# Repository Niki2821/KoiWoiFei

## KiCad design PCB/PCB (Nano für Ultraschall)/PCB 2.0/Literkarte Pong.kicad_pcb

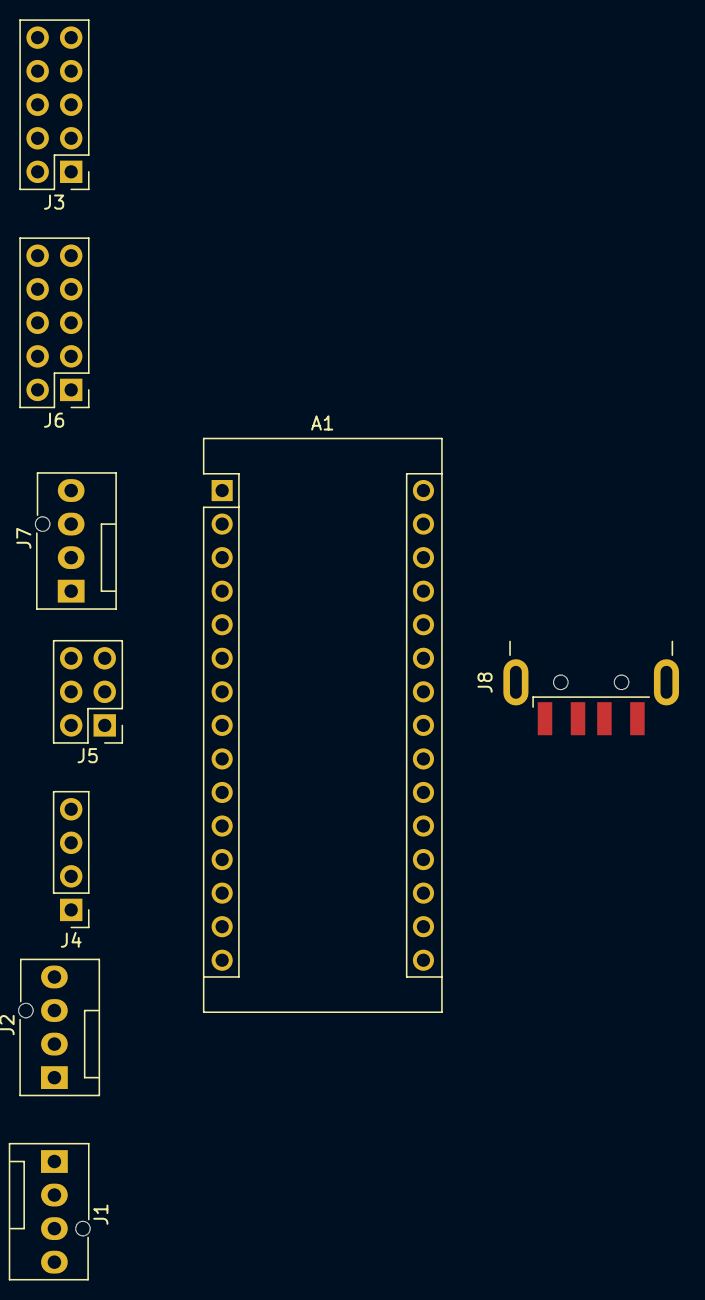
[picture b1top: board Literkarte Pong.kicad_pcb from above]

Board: 2 copper layers, 9 parts (0 on the bottom side), 16 nets, no tracks yet.

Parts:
A1: Arduino_Nano_v3.x; Arduino_Nano
J1: U4; FanPinHeader_1x04_P2.54mm_Vertical
J2: U3; FanPinHeader_1x04_P2.54mm_Vertical
J3, J6: Conn_02x05_Odd_Even; PinHeader_2x05_P2.54mm_Vertical
J4: U2; PinHeader_1x04_P2.54mm_Vertical
J5: Conn_02x03_Odd_Even; PinHeader_2x03_P2.54mm_Vertical
J7: U1; FanPinHeader_1x04_P2.54mm_Vertical
J8: USB_B; USB_A_CNCTech_1001-011-01101_Horizontal

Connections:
GND: A1.29, J1.1, J2.4, J3.1, J3.2, J4.4, J5.5, J5.6, J6.1, J6.2, J7.4, J8.4
unnamed: A1.1, J3.7, J3.8
unnamed: A1.2, J6.7, J6.8
unnamed: A1.5, J7.3
unnamed: A1.6, J7.2
unnamed: A1.7, J5.3, J5.4
unnamed: A1.8, J4.3
unnamed: A1.9, J4.2
unnamed: A1.10, J2.3
unnamed: A1.11, J2.2
unnamed: A1.12, J1.2
unnamed: A1.13, J1.3
unnamed: J3.3, J3.4
unnamed: J3.5, J3.6, J6.5, J6.6
unnamed: J6.3, J6.4
VCC: A1.27, J1.4, J2.1, J3.9, J3.10, J4.1, J5.1, J5.2, J6.9, J6.10, J7.1, J8.1

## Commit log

2022-05-13 filr files hochladen
    ja
2022-05-13 Intro Präsentation
